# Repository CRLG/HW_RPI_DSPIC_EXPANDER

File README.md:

# HW_RPI_DSPIC_EXPANDER
Extension dsPIC (GPIO / analog / codeur) pour Raspberry Pi

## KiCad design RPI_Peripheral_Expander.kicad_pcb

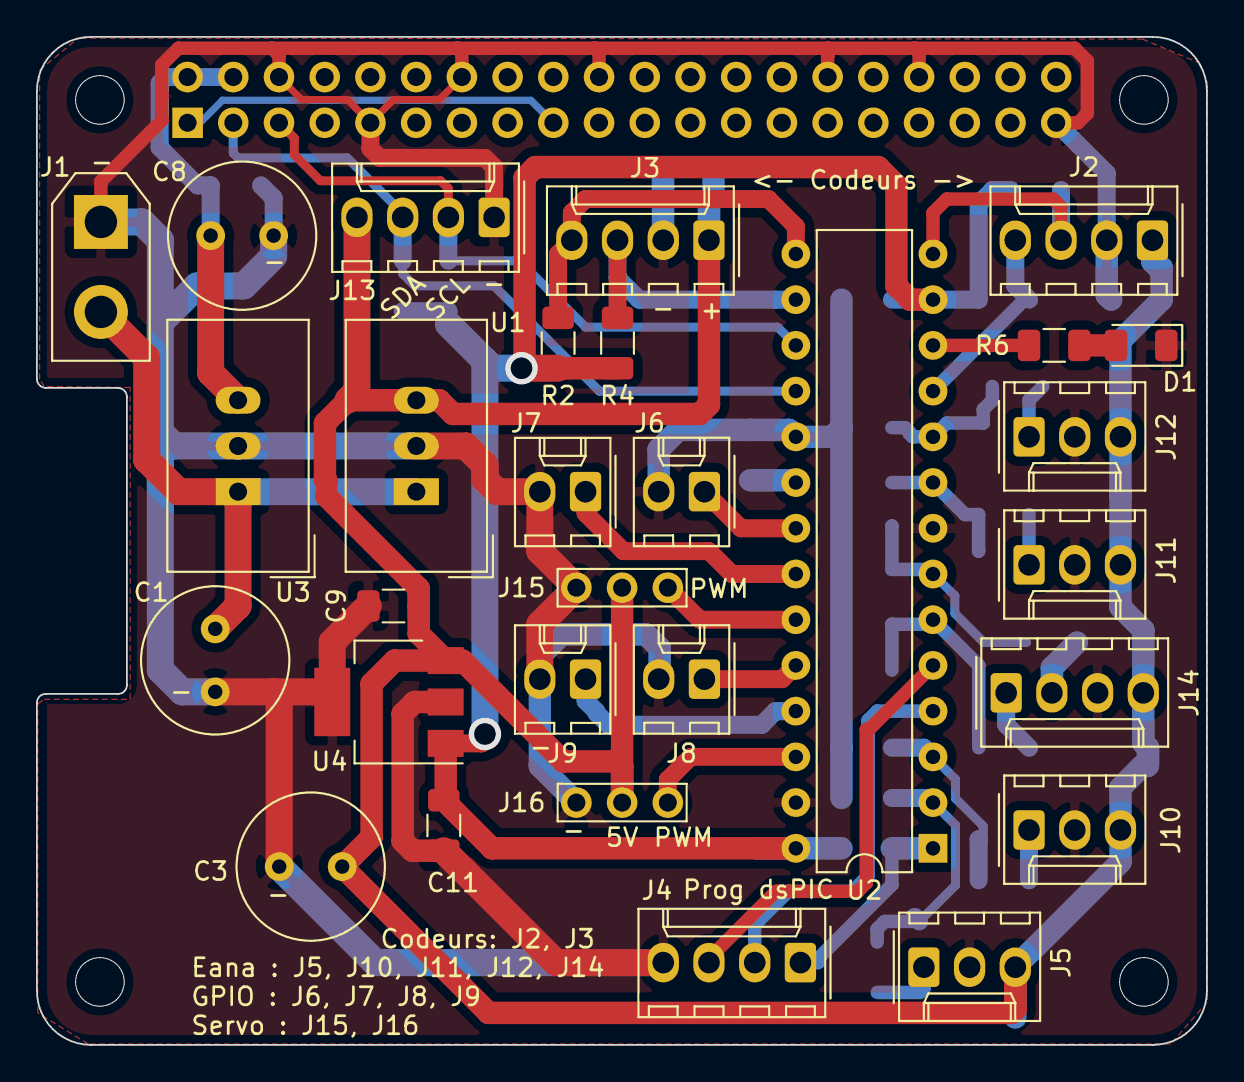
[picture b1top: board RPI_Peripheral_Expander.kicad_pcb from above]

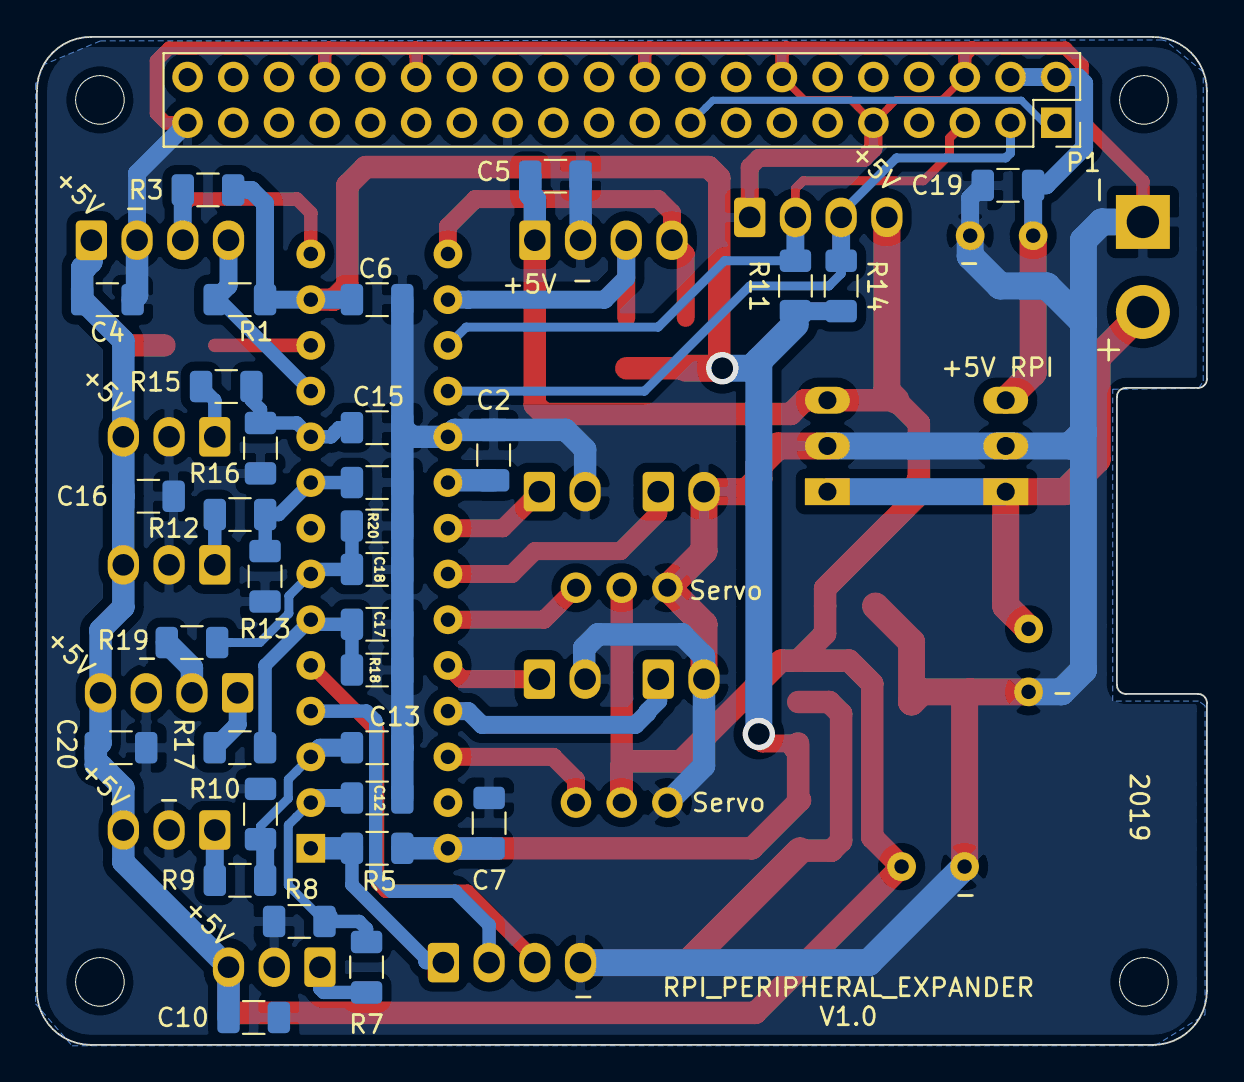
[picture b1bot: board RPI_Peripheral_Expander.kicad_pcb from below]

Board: 2 copper layers, 65.0 x 56.0 mm, 66 parts (33 on the bottom side), 36 nets.

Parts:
C1, C3, C8: 220u; C_Radial_D8.0mm_H11.5mm_P3.50mm
C2: 10u; C_1206_3216Metric
C4, C5, C10, C16, C20: 47u; C_1206_3216Metric
C6, C7, C19: 100n; C_1206_3216Metric
C9, C11: 1u; C_1206_3216Metric
C12, C13, C14, C15, C17, C18: Value; C_1206_3216Metric
D1: LED; LED_1206_3216Metric
J1: Conn_XT30; AMASS_XT30UPB-M_1x02_P5.0mm_Vertical
J2, J3, J4, J13, J14: Conn_01x04; Molex_KK-254_AE-6410-04A_1x04_P2.54mm_Vertical
J5, J10, J11, J12: Conn_01x03; Molex_KK-254_AE-6410-03A_1x03_P2.54mm_Vertical
J6, J7, J8, J9: Conn_01x02; Molex_KK-254_AE-6410-02A_1x02_P2.54mm_Vertical
J15, J16: Conn_01x03; Servomotor-3x254
MK1, MK2, MK3, MK4: M2.5; MountingHole_2.7mm_M2.5
P1: Conn_02x20_Odd_Even; PinSocket_2x20_P2.54mm_Vertical
R1, R2, R3, R4, R5: 10k; R_1206_3216Metric
R6, R11, R14: 4.7k; R_1206_3216Metric
R7, R8, R9, R10, R12, R13, R15, R16, R17, R18, R19, R20: R; R_1206_3216Metric
U1, U3: TSR_2-2450; Converter_DCDC_TRACO_TSR-2_THT
U2: DSPIC33FJ128MC802-xSP; DIP-28_W7.62mm
U4: MCP1804x-3302xDB; SOT-223-3_TabPin2

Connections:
+3V3: P1.1, P1.17
+5V: C3.1, C4.2, C5.2, C9.1, C10.2, C16.2, C20.2, J2.1, J3.1, J5.3, J10.3, J11.3, J12.3, J13.4, J14.4, J15.2, J16.2, U1.3, U4.3
/3.3V_dsPIC: C6.1, C7.2, C11.1, R1.2, R2.2, R3.2, R4.2, R5.1, R11.2, R14.2, U2.13, U2.28, U4.1
/+5V_RPI: C8.1, C19.2, P1.2, P1.4, U3.3
/Codeur1_A: J2.4, R1.1, U2.11
/Codeur1_B: J2.3, R3.1, U2.14
/Codeur2_A: J3.4, R2.1, U2.15
/Codeur2_B: J3.3, R4.1, U2.16
/Eana1: J5.1, R7.1
/Eana1f: C12.2, R7.2, R8.1, U2.2
/Eana2: J10.1, R9.1
/Eana2f: C13.2, R9.2, R10.1, U2.3
/Eana3: J11.1, R12.1
/Eana3f: C14.2, R12.2, R13.1, U2.9
/Eana4: J12.1, R15.1
/Eana4f: C15.2, R15.2, R16.1, U2.10
/Eana5: J14.1, R17.1
/Eana5f: C17.2, R17.2, R18.1, U2.6
/Eana6: J14.2, R19.1
/Eana6f: C18.2, R19.2, R20.1, U2.7
/GPIO1: J6.1, U2.21
/GPIO2: J7.1, U2.22
/GPIO3: J8.1, U2.24
/GPIO4: J9.1, U2.25
/I2C_SCL1: J13.2, P1.5, R11.1, U2.17
/I2C_SDA1: J13.3, P1.3, R14.1, U2.18
/SPWM1: J15.1, U2.23
/SPWM2: J16.1, U2.26
/VBAT: C1.1, J1.2, U1.1, U3.1
/dsPIC_MCLR: J4.1, R5.2, U2.1
/dsPIC_PGEC1: J4.3, U2.5
/dsPIC_PGED1: J4.2, U2.4
GND: C1.2, C2.2, C3.2, C4.1, C5.1, C6.2, C7.1, C8.2, C9.2, C10.1, C11.2, C12.1, C13.1, C14.1, C15.1, C16.1, C17.1, C18.1, C19.1, C20.1, D1.1, J1.1, J2.2, J3.2, J4.4, J5.2, J6.2, J7.2, J8.2, J9.2, J10.2, J11.2, J12.2, J13.1, J14.3, J15.3, J16.3, P1.6, P1.9, P1.14, P1.20, P1.25, P1.30, P1.34, P1.39, R8.2, R10.2, R13.2, R16.2, R18.2, R20.2, U1.2, U2.8, U2.19, U2.27, U3.2, U4.2
unnamed: C2.1, U2.20
unnamed: D1.2, R6.1
unnamed: R6.2, U2.12

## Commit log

2019-08-11 Ajout du sous-module KICAD_LIB
2019-08-11 Version initiale du projet
2019-08-11 Mise à jour fichiers gerber
2019-08-25 Résistance LED dsPIC passée à 470 Ohms
